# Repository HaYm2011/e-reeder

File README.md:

# e-reeder
a e-reader... aka chapri kindle
So my projects basically a e-reader like a kindle but a lot bulkier, and it uses a 4-3inch e-paper display, an esp32 s3, 3 2000mah li-ion batteries, it also uses 2 TOF VL53LOX sensors for swipe movements for swiping pages or changing the content displayed on the screen, I used kicad to make the pcb which connects all th parts and fusion 360 for the 3d printed chassis

## Bill of Materials (BOM)

| Item | Component | Vendor | Unit Price (INR) | Qty | Total Price (INR) | Purpose / Notes |
| :--- | :--- | :--- | :---: | :---: | :---: | :--- |
| 1 | [4.3" Serial Interface Electronic Paper Display](https://robocraze.com/products/4-3in-serial-interface-electronic-paper-display) | Robocraze | ₹4,699.00 | 1 | ₹4,699.00 | 800×600 UART e-paper screen |
| 2 | [7Semi ESP32-S3 Dev Board (N8R8, Dual Type-C)](https://robocraze.com/products/7semi-esp32-s3-dev-boardc-1-n8r8-wifi-bluetooth-dual-usb-c-rgb-led) | Robocraze | ₹899.00 | 1 | ₹899.00 | Primary microcontroller (8MB Flash, 8MB PSRAM) |
| 3 | [VL53L0X TOF Laser Distance Sensor](https://robu.in/product/vl53l0x-tof-based-lidar-laser-distance-sensor/) | Robu.in | ₹119.00 | 2 | ₹238.00 | Left & right gesture detection for page turns |
| 4 | [3.7V 2000mAh 18650 Li-Ion Battery](https://robocraze.com/products/3-7v-2000mah-18650-li-ion-battery) | Robocraze | ₹69.00 | 3 | ₹207.00 | Rechargeable battery cells |
| 5 | [18650 3-Cell Holder Without Cover](https://robocraze.com/products/18650-3-cell-holder-charger-without-cover) | Robocraze | ₹33.00 | 1 | ₹33.00 | Series enclosure/leads for 3× 18650 cells |
| 6 | Custom 3D Printed Enclosure:  https://robu.in/product/3d-printing-service1/ | Robocraze 3d-printing service | ₹700.00 | 1 | ₹700.00 | Front & back shell housing |
| **Total** | | | | **9** | **₹6,776.00** | *(Excluding shipping)* |

for the 3d print i have checked the cost of printing it with 0.2 standard quality 20% infil PLA(black): it amounts to ₹700

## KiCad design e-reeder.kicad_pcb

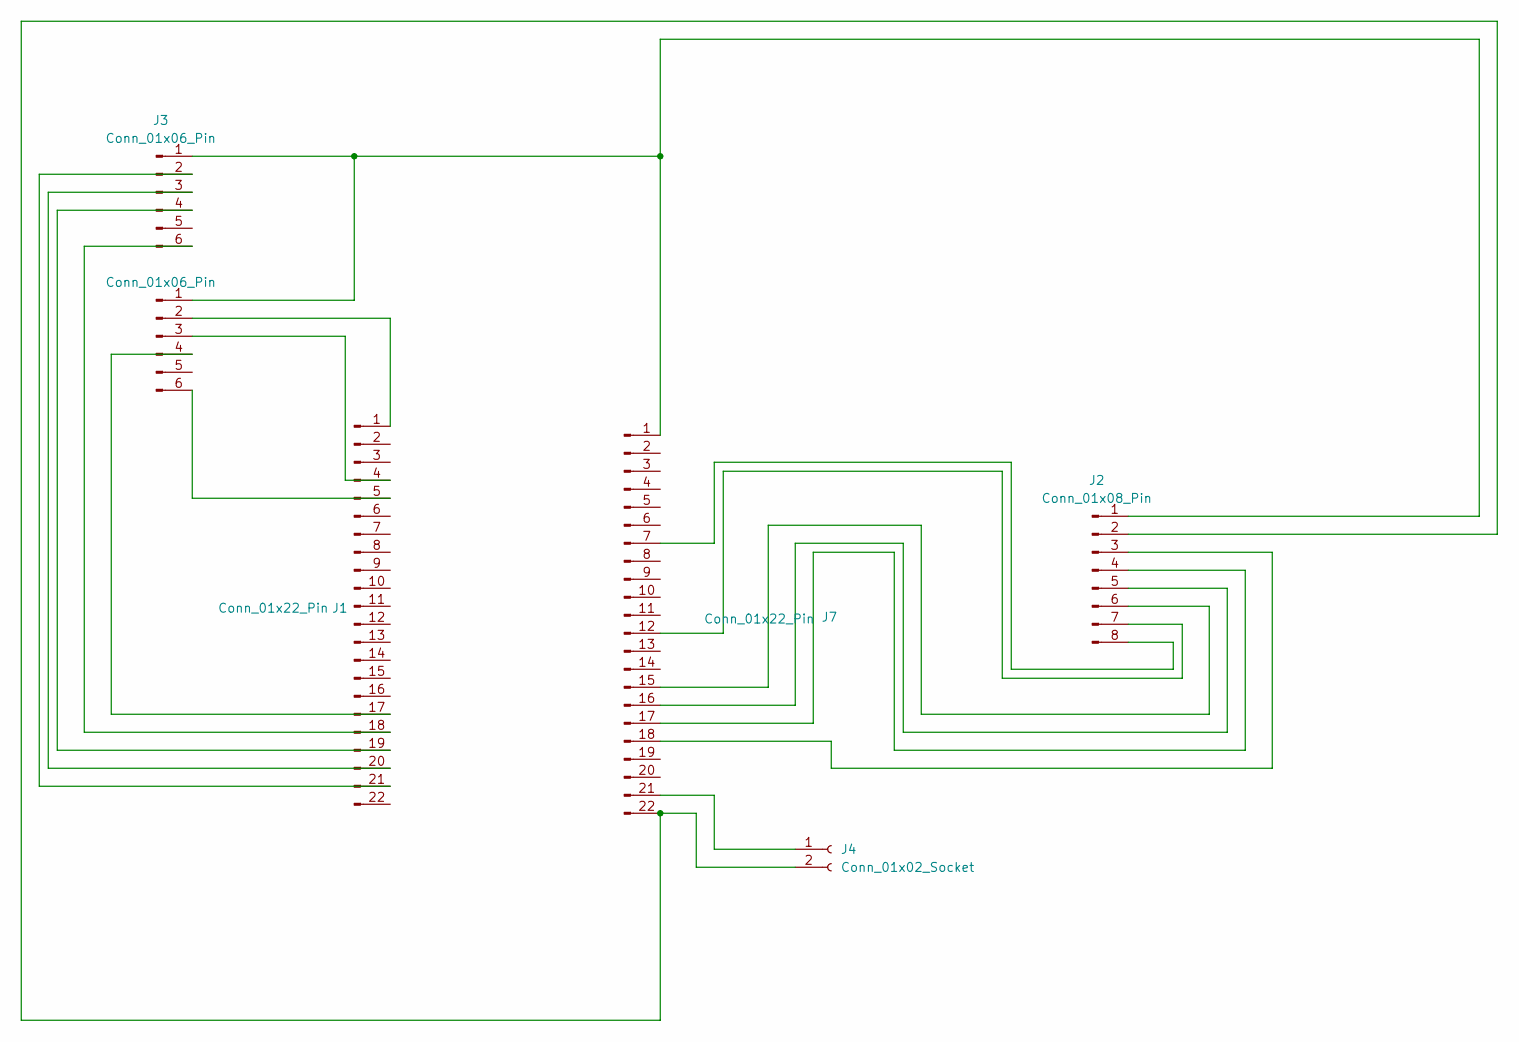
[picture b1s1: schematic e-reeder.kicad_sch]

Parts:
J1, J7: Conn_01x22_Pin; PinSocket_1x22_P2.54mm_Vertical
J2: Conn_01x08_Pin; PinSocket_1x08_P2.54mm_Vertical
J3, J5: Conn_01x06_Pin; PinSocket_1x06_P2.54mm_Vertical
J4: Conn_01x02_Socket; JST_PH_S2B-PH-K_1x02_P2.00mm_Horizontal

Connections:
unnamed: J1.1, J5.2
unnamed: J1.4, J5.3
unnamed: J1.5, J5.6
unnamed: J1.17, J5.4
unnamed: J1.18, J3.6
unnamed: J1.19, J3.4
unnamed: J1.20, J3.3
unnamed: J1.21, J3.2
unnamed: J2.1, J3.1, J5.1, J7.1
unnamed: J2.2, J4.2, J7.22
unnamed: J2.3, J7.18
unnamed: J2.4, J7.17
unnamed: J2.5, J7.16
unnamed: J2.6, J7.15
unnamed: J2.7, J7.12
unnamed: J2.8, J7.7
unnamed: J4.1, J7.21

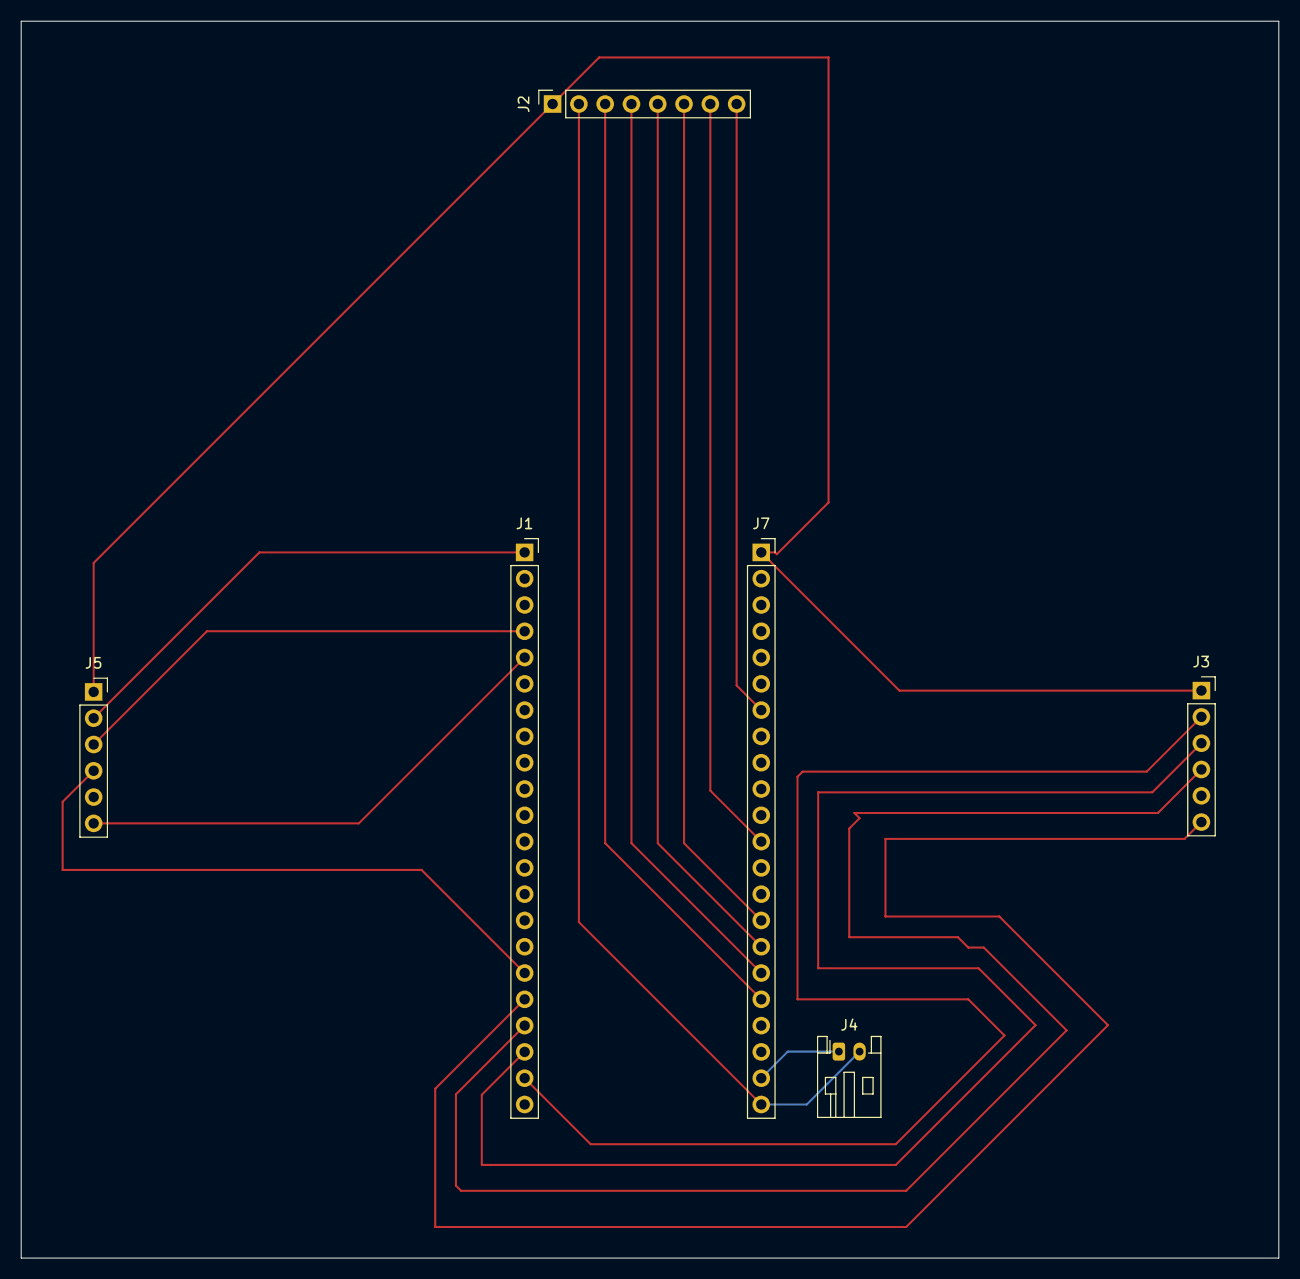
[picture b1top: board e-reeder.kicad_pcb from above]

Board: 2 copper layers, 121.5 x 119.5 mm, 6 parts (0 on the bottom side), 17 nets.

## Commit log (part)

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2026-06-08 Add files via upload
    added journal from hackclub devlog
